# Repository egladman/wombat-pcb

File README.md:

# The Wombat

The Wombat is my 40% daily driver that I've been using for 3+ years.

### Project Goals
- Open source design. It was important that I use an open source EDA too.
- Standard staggered row. I see so many mis-aligned 40% keyboards, I have no clue how people can effectively type on them.
- No `2.75u` keys. I find `2.75u` keycaps to wobble too much for everyday typing (even with geniune GMK stabs), therefore the longest key on the Wombat is `2.25u`.
- Dedicated bracket keys (i.e. `[`, `]`). I'm a software engineer and I find these keys invaluable.
- HHKB style arrow keys. I've become super fond of this layout ever since owning my first HHKB.
- Non-fullsize space bar. I find a standard `6.25u` (or god forbid anything larger) to be a waste of space. A little part of me dies each time I see a `7u` spacebar on a 40%.
- Case friendly design. By extending the header pins from the board we're able to make the female usb port flush with cases. 
- Side removable cable. I typicallly use my 40% boards when I'm using my laptop. By having the usb cable connect on the left, I'm able to push the keyboard up against my laptop saving valuable space. Sorry left handers :frowning:
- MX/Alps compatibility. It's so easy to support Alps, why not...
- Pro Micro compatability. They're cheap and ubiquitous; headers are infintely easier to solder than SMT for a novice.
- Backspace inline with spacebar. I prototyped multiple layouts before ultimately deciding on this. That was three years ago and I've been using this layout ever since.
- TMK/QMK compatibility.
- LED backlighting. Only the Alphas are backlight, this is a comprise to retain support for multiple bottom rows.
- Low profile design. Keyboards built with Pro Micros tend to be thick. By mounting the controller upside we're able to reduce the required clearance to `6mm`.
- Proton-C and Elite-C compatibility. Due to how we mount the microcontroller upside down, this wasn't supported in Rev A. (Rev A source code has since been lost. RIP)

### Drawbacks

- Lack of keycap compatibility. Good luck finding properly labeled modifiers. This isn't a deal breaker for me since I mostly type on DSA blanks.
  - The bottom row variant introduced in Rev C partially helps mitigate this issue.
- The right shift has been relocated to the bottom row. I prioritized the placement of `FN1` (think HHKB).
- I'm sure there are other drawbacks, I think I've just become blind to them. I've been using this layout for 3+ years without problems.

### Changes

#### Rev C

- Multiple bottom rows now supported.
- Backlighting Support (Alphas only)
- Additional pinouts (three LEDs) are broken out for the Proton-C and Elite-C. The Pro Micro can't utilize these pins since we're maxing out the pins. These LEDs are intended to be used as layer indicators.

#### Rev B

- Backlighting Support
- Pro Micro low profile mount. Every `0.1mm` counts.

### Known Issues

#### Rev B

- The LED through holes on top row are slightly misaligned. Be patient when inserting the anode.
- Incorrect footprint for `D1`. It's solderable, but tricky.
- **IMPORTANT:** Ground for backlighting is misrouted. Backlighting/Keyboard is inoperable until ground trace is severed. See red lines.

### Layout

### PCB

*Ignore the dirty residual flux, these pictures were taken mid-build before the boards were cleaned.*

### Components

- 35 `SMD 0805` 300ohms Resistors. [example](https://www.mouser.com/ProductDetail/panasonic/erj-6enf3000v/?qs=50QC8w71jAu7HdivK4y78A%3D%3D&countrycode=US&currencycode=USD)
- 46 `SOD-123` 1N4148 Diodes. [example](https://www.mouser.com/ProductDetail/diodes-incorporated/1n4148w-7-f/?qs=LHX0FizJzg7Ae9ZM8LTAWw%3D%3D&countrycode=US&currencycode=USD)
- 1 Microcontroller
  - Pro Micro [example](https://www.sparkfun.com/products/12640)
  - Proton-C [example](https://olkb.com/parts/qmk-proton-c)
  - Elite-C [example](https://keeb.io/products/elite-c-usb-c-pro-micro-replacement-arduino-compatible-atmega32u4?variant=31151566389342) *I personally haven't tested compatibility, but it should work*
- Header pins `PTH, 0.1`
- SMD Momentary NO Switch (Reset Button) *I need to look up the part number I used.*

If you choose to make a back from an extra pcb you'll need:
- 8 M2x6mm female to female threaded spacers
- 16 M2x4mm screws
- Blue loctite or M2 lock washers doesn't hurt...

### Firmware

- [QMK](https://github.com/egladman/qmk_firmware/tree/wombat-support/keyboards/wombat).
- [TMK](https://github.com/egladman/wombat-tmk). My TMK fork is super old, and is only here for archival purposes. Use QMK.

### Dependencies

[keebs.pretty](https://github.com/egladman/keebs.pretty)

### License

[CERN Open Hardware Licence v1.2 ](https://github.com/egladman/wombat-pcb/blob/revc/LICENSE)

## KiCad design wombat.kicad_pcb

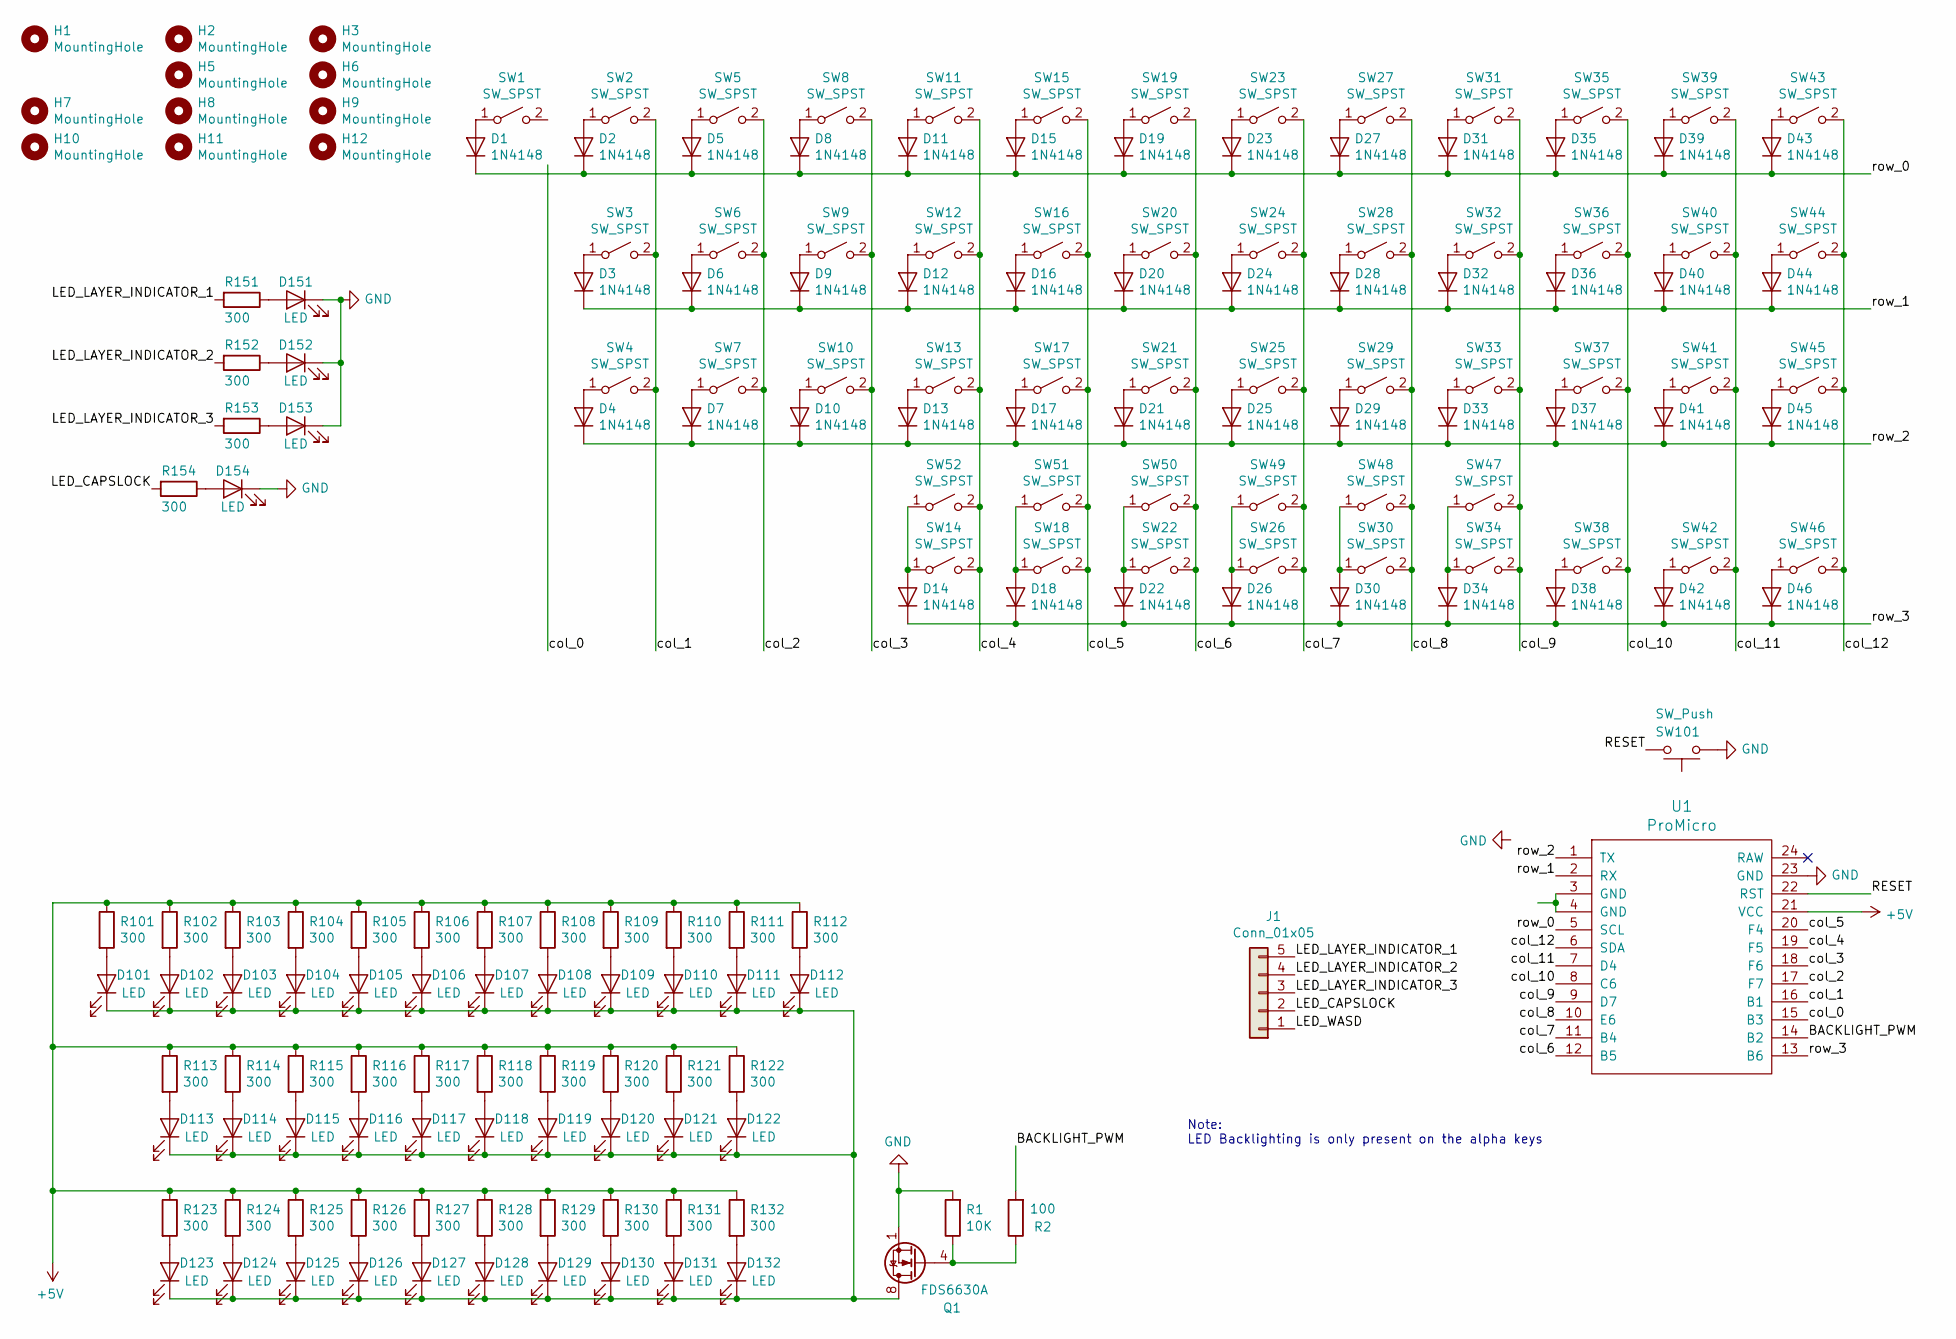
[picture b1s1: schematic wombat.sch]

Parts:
D1, D2, D3, D4, D5, D6, D7, D8, D9, D10, D11, D12, D13, D14, D15, D16, D17, D18, D19, D20, D21, D22, D23, D24, D25, D26, D27, D28, D29, D30, D31, D32, D33, D34, D35, D36, D37, D38, D39, D40, D41, D42, D43, D44, D45, D46: 1N4148; D_0805_2012Metric_Pad1.15x1.40mm_HandSolder
D101, D102, D103, D104, D105, D106, D107, D108, D109, D110, D111, D112, D113, D114, D115, D116, D117, D118, D119, D120, D121, D122, D123, D124, D125, D126, D127, D128, D129, D130, D131, D132, D154: LED; LED_D2.0mm_W4.8mm_H2.5mm_FlatTop_Reverse_Polarity
D151, D152, D153: LED; LED_0805_2012Metric_Pad1.15x1.40mm_HandSolder
H1, H2, H3, H5, H6, H7, H8, H9, H10, H11, H12: MountingHole; MountingHole_2.2mm_M2_DIN965_Pad_Oval
J1: Conn_01x05; PinSocket_1x05_P2.00mm_Vertical
Q1: FDS6630A; SOIC-8_3.9x4.9mm_P1.27mm
R1: 10K; R_0805_2012Metric_Pad1.15x1.40mm_HandSolder
R2: 100; R_0805_2012Metric_Pad1.15x1.40mm_HandSolder
R101, R102, R103, R104, R105, R106, R107, R108, R109, R110, R111, R112, R113, R114, R115, R116, R117, R118, R119, R120, R121, R122, R123, R124, R125, R126, R127, R128, R129, R130, R131, R132, R151, R152, R153: 300; R_0805_2012Metric_Pad1.15x1.40mm_HandSolder
R154: 300; R_0805_2012Metric_Pad1.15x1.40mm_HandSolder_Double_Sided
SW1, SW2, SW5, SW6, SW7, SW8, SW9, SW10, SW11, SW12, SW13, SW14, SW15, SW16, SW17, SW19, SW20, SW21, SW23, SW24, SW25, SW27, SW28, SW29, SW31, SW32, SW33, SW35, SW36, SW37, SW39, SW40, SW41, SW43: SW_SPST; Mx_Alps_100
SW3, SW45: SW_SPST; Mx_Alps_175
SW4, SW18, SW22, SW26, SW38, SW42, SW44, SW46, SW49, SW50, SW51, SW52: SW_SPST; Mx_Alps_125
SW30, SW34: SW_SPST; Mx_Alps_225_Inverted_Stabs
SW47: SW_SPST; Mx_Alps_200
SW48: SW_SPST; Mx_Alps_225
SW101: SW_Push; SW_SPST_EVQP0
U1: ProMicro; Pro_Micro

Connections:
+5V: R101.1, R102.1, R103.1, R104.1, R105.1, R106.1, R107.1, R108.1, R109.1, R110.1, R111.1, R112.1, R113.1, R114.1, R115.1, R116.1, R117.1, R118.1, R119.1, R120.1, R121.1, R122.1, R123.1, R124.1, R125.1, R126.1, R127.1, R128.1, R129.1, R130.1, R131.1, R132.1, U1.21 (VCC)
/BACKLIGHT_PWM: R2.2, U1.14 (B2)
/LED_CAPSLOCK: J1.2, R154.2
/LED_LAYER_INDICATOR_1: J1.5, R151.2
/LED_LAYER_INDICATOR_2: J1.4, R152.2
/LED_LAYER_INDICATOR_3: J1.3, R153.2
/LED_WASD: J1.1
/RESET: SW101.2, U1.22 (RST)
/col_0: U1.15 (B3)
/col_1: SW2.2 (B), SW3.2 (B), SW4.2 (B), U1.16 (B1)
/col_2: SW5.2 (B), SW6.2 (B), SW7.2 (B), U1.17 (F7)
/col_3: SW8.2 (B), SW9.2 (B), SW10.2 (B), U1.18 (F6)
/col_4: SW11.2 (B), SW12.2 (B), SW13.2 (B), SW14.2 (B), SW52.2 (B), U1.19 (F5)
/col_5: SW15.2 (B), SW16.2 (B), SW17.2 (B), SW18.2 (B), SW51.2 (B), U1.20 (F4)
/col_6: SW19.2 (B), SW20.2 (B), SW21.2 (B), SW22.2 (B), SW50.2 (B), U1.12 (B5)
/col_7: SW23.2 (B), SW24.2 (B), SW25.2 (B), SW26.2 (B), SW49.2 (B), U1.11 (B4)
/col_8: SW27.2 (B), SW28.2 (B), SW29.2 (B), SW30.2 (B), SW48.2 (B), U1.10 (E6)
/col_9: SW31.2 (B), SW32.2 (B), SW33.2 (B), SW34.2 (B), SW47.2 (B), U1.9 (D7)
/col_10: SW35.2 (B), SW36.2 (B), SW37.2 (B), SW38.2 (B), U1.8 (C6)
/col_11: SW39.2 (B), SW40.2 (B), SW41.2 (B), SW42.2 (B), U1.7 (D4)
/col_12: SW43.2 (B), SW44.2 (B), SW45.2 (B), SW46.2 (B), U1.6 (SDA)
/row_0: D1.1 (K), D2.1 (K), D5.1 (K), D8.1 (K), D11.1 (K), D15.1 (K), D19.1 (K), D23.1 (K), D27.1 (K), D31.1 (K), D35.1 (K), D39.1 (K), D43.1 (K), U1.5 (SCL)
/row_1: D3.1 (K), D6.1 (K), D9.1 (K), D12.1 (K), D16.1 (K), D20.1 (K), D24.1 (K), D28.1 (K), D32.1 (K), D36.1 (K), D40.1 (K), D44.1 (K), U1.2 (RX)
/row_2: D4.1 (K), D7.1 (K), D10.1 (K), D13.1 (K), D17.1 (K), D21.1 (K), D25.1 (K), D29.1 (K), D33.1 (K), D37.1 (K), D41.1 (K), D45.1 (K), U1.1 (TX)
/row_3: D14.1 (K), D18.1 (K), D22.1 (K), D26.1 (K), D30.1 (K), D34.1 (K), D38.1 (K), D42.1 (K), D46.1 (K), U1.13 (B6)
GND: D151.1 (K), D152.1 (K), D153.1 (K), D154.1 (K), Q1.1 (S), Q1.2 (S), Q1.3 (S), R1.2, SW101.1, U1.23 (GND)
unnamed: D1.2 (A), SW1.1 (A)
unnamed: D2.2 (A), SW2.1 (A)
unnamed: D3.2 (A), SW3.1 (A)
unnamed: D4.2 (A), SW4.1 (A)
unnamed: D5.2 (A), SW5.1 (A)
unnamed: D6.2 (A), SW6.1 (A)
unnamed: D7.2 (A), SW7.1 (A)
unnamed: D8.2 (A), SW8.1 (A)
unnamed: D9.2 (A), SW9.1 (A)
unnamed: D10.2 (A), SW10.1 (A)
unnamed: D11.2 (A), SW11.1 (A)
unnamed: D12.2 (A), SW12.1 (A)
unnamed: D13.2 (A), SW13.1 (A)
unnamed: D14.2 (A), SW14.1 (A), SW52.1 (A)
unnamed: D15.2 (A), SW15.1 (A)
unnamed: D16.2 (A), SW16.1 (A)
unnamed: D17.2 (A), SW17.1 (A)
unnamed: D18.2 (A), SW18.1 (A), SW51.1 (A)
unnamed: D19.2 (A), SW19.1 (A)
unnamed: D20.2 (A), SW20.1 (A)
unnamed: D21.2 (A), SW21.1 (A)
unnamed: D22.2 (A), SW22.1 (A), SW50.1 (A)
unnamed: D23.2 (A), SW23.1 (A)
unnamed: D24.2 (A), SW24.1 (A)
unnamed: D25.2 (A), SW25.1 (A)
unnamed: D26.2 (A), SW26.1 (A), SW49.1 (A)
unnamed: D27.2 (A), SW27.1 (A)
unnamed: D28.2 (A), SW28.1 (A)
unnamed: D29.2 (A), SW29.1 (A)
unnamed: D30.2 (A), SW30.1 (A), SW48.1 (A)
unnamed: D31.2 (A), SW31.1 (A)
unnamed: D32.2 (A), SW32.1 (A)
unnamed: D33.2 (A), SW33.1 (A)
unnamed: D34.2 (A), SW34.1 (A), SW47.1 (A)
unnamed: D35.2 (A), SW35.1 (A)
unnamed: D36.2 (A), SW36.1 (A)
unnamed: D37.2 (A), SW37.1 (A)
unnamed: D38.2 (A), SW38.1 (A)
unnamed: D39.2 (A), SW39.1 (A)
unnamed: D40.2 (A), SW40.1 (A)
unnamed: D41.2 (A), SW41.1 (A)
unnamed: D42.2 (A), SW42.1 (A)
unnamed: D43.2 (A), SW43.1 (A)
unnamed: D44.2 (A), SW44.1 (A)
unnamed: D45.2 (A), SW45.1 (A)
unnamed: D46.2 (A), SW46.1 (A)
unnamed: D101.1 (K), D102.1 (K), D103.1 (K), D104.1 (K), D105.1 (K), D106.1 (K), D107.1 (K), D108.1 (K), D109.1 (K), D110.1 (K), D111.1 (K), D112.1 (K), D113.1 (K), D114.1 (K), D115.1 (K), D116.1 (K), D117.1 (K), D118.1 (K), D119.1 (K), D120.1 (K), D121.1 (K), D122.1 (K), D123.1 (K), D124.1 (K), D125.1 (K), D126.1 (K), D127.1 (K), D128.1 (K), D129.1 (K), D130.1 (K), D131.1 (K), D132.1 (K), Q1.5 (D), Q1.6 (D), Q1.7 (D), Q1.8 (D)
unnamed: D101.2 (A), R101.2
unnamed: D102.2 (A), R102.2
unnamed: D103.2 (A), R103.2
unnamed: D104.2 (A), R104.2
unnamed: D105.2 (A), R105.2
unnamed: D106.2 (A), R106.2
unnamed: D107.2 (A), R107.2
unnamed: D108.2 (A), R108.2
unnamed: D109.2 (A), R109.2
unnamed: D110.2 (A), R110.2
unnamed: D111.2 (A), R111.2
unnamed: D112.2 (A), R112.2
unnamed: D113.2 (A), R113.2
unnamed: D114.2 (A), R114.2
unnamed: D115.2 (A), R115.2
unnamed: D116.2 (A), R116.2
unnamed: D117.2 (A), R117.2
unnamed: D118.2 (A), R118.2
unnamed: D119.2 (A), R119.2
unnamed: D120.2 (A), R120.2
unnamed: D121.2 (A), R121.2
unnamed: D122.2 (A), R122.2
unnamed: D123.2 (A), R123.2
unnamed: D124.2 (A), R124.2
unnamed: D125.2 (A), R125.2
unnamed: D126.2 (A), R126.2
unnamed: D127.2 (A), R127.2
unnamed: D128.2 (A), R128.2
unnamed: D129.2 (A), R129.2
unnamed: D130.2 (A), R130.2
unnamed: D131.2 (A), R131.2
unnamed: D132.2 (A), R132.2
unnamed: D151.2 (A), R151.1
unnamed: D152.2 (A), R152.1
unnamed: D153.2 (A), R153.1
unnamed: D154.2 (A), R154.1
unnamed: Q1.4 (G), R1.1, R2.1
unnamed: U1.3 (GND), U1.4 (GND)

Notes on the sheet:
Note: LED Backlighting is only present on the alpha keys

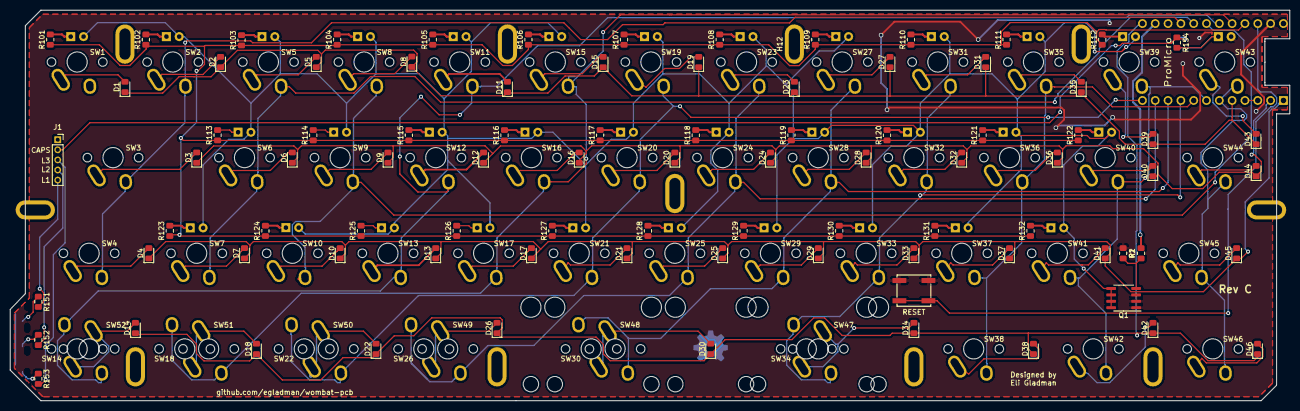
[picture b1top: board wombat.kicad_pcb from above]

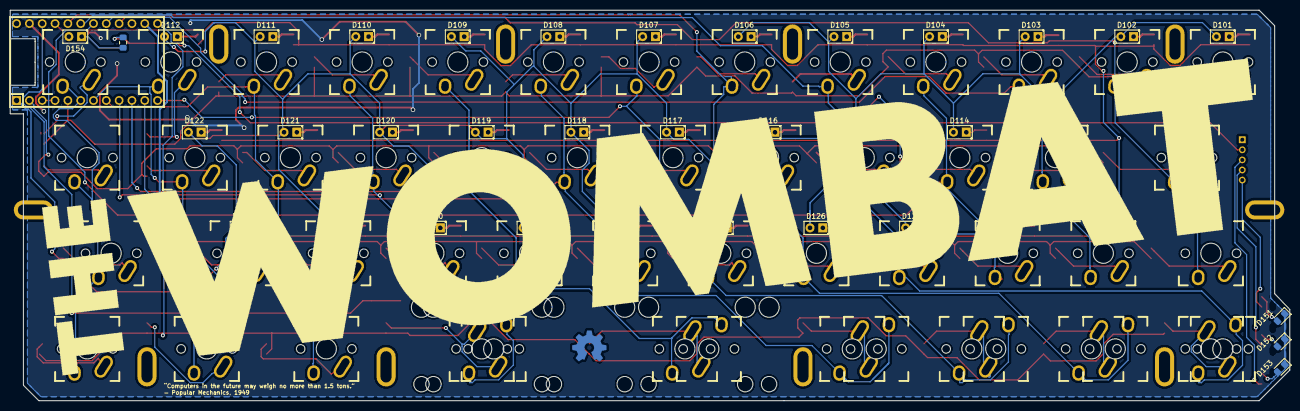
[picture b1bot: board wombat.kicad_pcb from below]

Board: 2 copper layers, 253.5 x 77.4 mm, 195 parts (92 on the bottom side), 109 nets.

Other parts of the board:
G1: LOGO; oshw_logo
G3: LOGO; wombat_logo
H101, H102, H103, H104: Mouse_Bite; Mouse_Bite_04MM_11
H105, H106: Mouse_Bite; Mouse_Bite_04MM_06

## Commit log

2019-11-15 recreated schematic
    revA schematic has been lost. so i had to recreate it
2019-11-15 annotate components
    associate symbols to footprints
2019-11-16 add pic of layout
2019-11-17 layout board
2019-11-17 change orientation of mc
2019-11-18 route traces
2019-11-18 Add ground zones
2019-11-18 adjust ground zones
    tweak ground zones near pro micro headers
2019-11-18 removed old asset
2019-11-18 Update wombat.kicad_pcb
    add addidtional silkscreen annotation for R113
2019-11-18 hide fab values
2019-11-19 added renders of PCB
2019-11-26 Support bottom row variant
2019-11-26 clean up silkscreen
2019-11-27 fix led placement on top row
2019-11-27 auto-route traces
2019-11-27 enhance docs
2019-11-27 spelling
2019-11-27 added license to readme
2019-11-27 added component list
2019-12-12 added con
2019-12-12 add pics of rev b
2019-12-12 change branch of qmk fork refrenced
2019-12-12 fix md formatting
2019-12-12 add note about bottom row
2019-12-13 add materials to list
2019-12-16 Prep for routing
    - North facing LEDs
    - invert stabilizers
    - New mounting holes (it's overkill, but i'd rather have options)
    - implemented transitor to drive LEDs
    - rename lib dir to wombat.pretty
    - map pinouts for capslock and layer indicator LEDs
2019-12-16 vertically align diodes on top row
2019-12-16 add photos of revb fix
2019-12-16 fix grammar
2019-12-16 add revc pic to readme
2019-12-16 clean up autorouted traces
2019-12-16 reposition oshw logo
2019-12-16 increase ground plane surface
2019-12-16 add no net copper fill
2019-12-16 Fix diode silkscreen
2019-12-16 add pcb render
2019-12-16 fix botched markdown
2019-12-29 tidy up schematic. no changes no circuit
